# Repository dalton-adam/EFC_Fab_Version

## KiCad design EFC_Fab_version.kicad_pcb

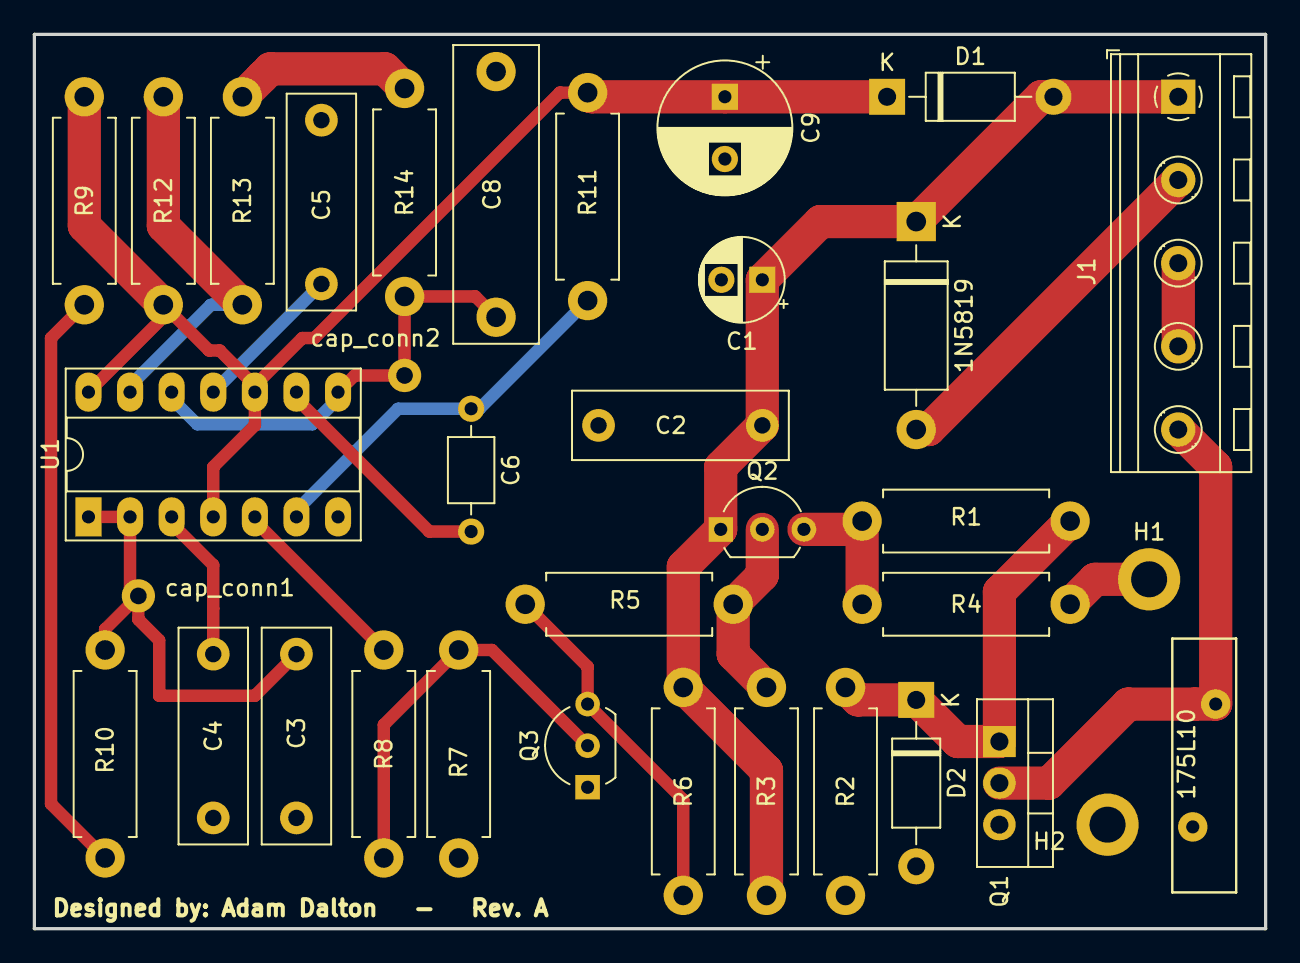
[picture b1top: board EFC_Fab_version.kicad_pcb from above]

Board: 2 copper layers, 75.2 x 54.6 mm, 35 parts (0 on the bottom side), 22 nets.

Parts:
1N5819: D_Schottky; D_DO-15_P12.70mm_Horizontal
175L10: Varistor; RV_Disc_D15.5mm_W3.9mm_P7.5mm
C1: 100u; CP_Radial_D5.0mm_P2.50mm
C2, C3, C4, C5: .1u; C_Rect_L13.0mm_W4.0mm_P10.00mm_FKS3_FKP3_MKS4
C6: .01; C_Axial_L3.8mm_D2.6mm_P7.50mm_Horizontal
C8: .33u; C_Rect_L18.0mm_W5.0mm_P15.00mm_FKS3_FKP3
C9: 470u; CP_Radial_D8.0mm_P3.80mm
D1: 1N4006; D_DO-41_SOD81_P10.16mm_Horizontal
D2: 1N4006_2; D_DO-41_SOD81_P10.16mm_Horizontal
H1: LED; MountingHole_2.2mm_M2_ISO14580_Pad
H2: GND; MountingHole_2.2mm_M2_ISO14580_Pad
J1: Screw_Terminal_01x05; TerminalBlock_RND_205-00235_1x05_P5.08mm_Horizontal
Q1: MJE13005G; TO-220-3_Vertical
Q2: 2N3906; TO-92L_Inline_Wide
Q3: 2N3904; TO-92L_Inline_Wide
R1: 10; R_Axial_DIN0411_L9.9mm_D3.6mm_P12.70mm_Horizontal
R2, R3, R4, R5, R6, R7, R8: 220; R_Axial_DIN0411_L9.9mm_D3.6mm_P12.70mm_Horizontal
R9: 4.7K; R_Axial_DIN0411_L9.9mm_D3.6mm_P12.70mm_Horizontal
R10: 150K; R_Axial_DIN0411_L9.9mm_D3.6mm_P12.70mm_Horizontal
R11: 18K; R_Axial_DIN0411_L9.9mm_D3.6mm_P12.70mm_Horizontal
R12: 18k; R_Axial_DIN0411_L9.9mm_D3.6mm_P12.70mm_Horizontal
R13: 470K; R_Axial_DIN0411_L9.9mm_D3.6mm_P12.70mm_Horizontal
R14: 2200K; R_Axial_DIN0411_L9.9mm_D3.6mm_P12.70mm_Horizontal
U1: NE556; DIP-14_W7.62mm_Socket_LongPads
cap_conn1, cap_conn2: MountingHole_Pad; MountingHole_2.2mm_M2_ISO14580_Pad

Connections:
/Vcc: C9.1, D1.1, R9.1, R11.1, R12.1, U1.4, U1.10, U1.14
Earth: 175L10.2, C1.2, C2.2, C3.2, C4.2, C5.2, C8.2, C9.2, D2.2, H2.1, Q1.3, Q3.1, R2.2, R7.2, U1.7
unnamed: 1N5819.1, C1.1, C2.1, D1.2, J1.1, Q2.1, R3.1, R6.1
unnamed: 1N5819.2, J1.2
unnamed: 175L10.1, J1.5, Q1.2
unnamed: C3.1, R10.2, U1.1, U1.2, cap_conn1.1
unnamed: C4.1, U1.3
unnamed: C5.1, U1.11
unnamed: C6.1, R11.2, U1.6
unnamed: C6.2, U1.9
unnamed: C8.1, R14.1, U1.8, U1.12, cap_conn2.1
unnamed: D2.1, Q1.1, R1.1, R2.1
unnamed: H1.1, R4.2
unnamed: J1.3, J1.4
unnamed: Q2.2, R3.2, R5.2
unnamed: Q2.3, R1.2, R4.1
unnamed: Q3.2, R7.1, R8.2
unnamed: Q3.3, R5.1, R6.2
unnamed: R8.1, U1.5
unnamed: R9.2, R10.1
unnamed: R12.2, R13.2, U1.13
unnamed: R13.1, R14.2

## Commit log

2020-05-01 Made a new repository for the EFC Fab Version
